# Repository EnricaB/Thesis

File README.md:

# Thesis
Thesis : Complessitá

---

### Clone this Repo

* navigate to your openFrameworks 0084 folder
  * `$ cd path/to/my_openFrameworks_0084/`
* inside this (root) folder, along side /apps /examples /addons etc, run: 
  * `$ git clone https://github.com/EnricaB/Thesis.git`
* now any OF apps inside of the openFrameworks folder of this repo will run fine

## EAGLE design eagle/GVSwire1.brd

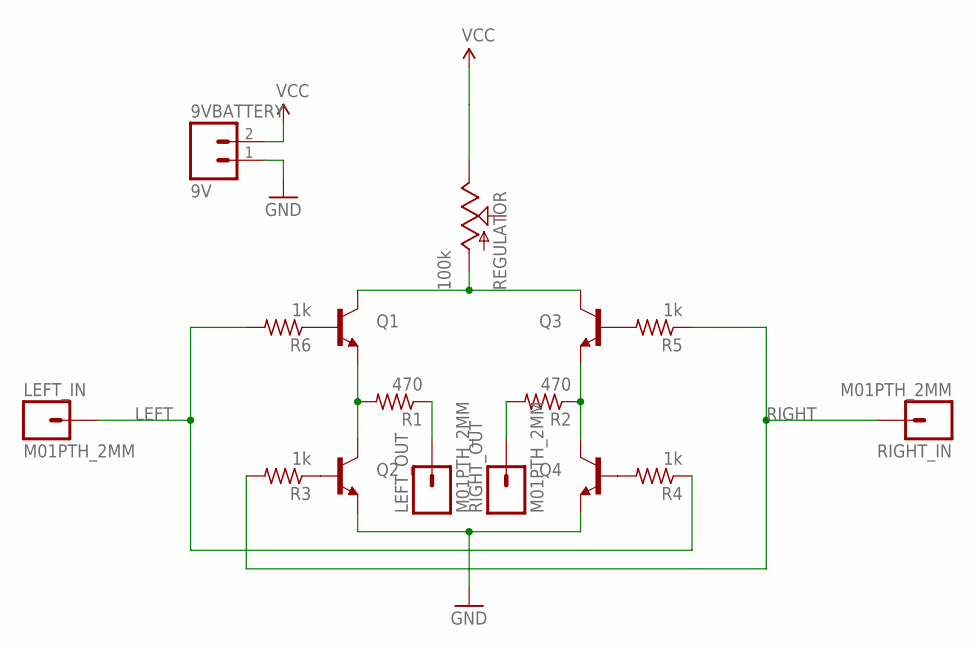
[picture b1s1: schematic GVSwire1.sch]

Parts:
9VBATTERY: 9V; 1X02_LONGPADS
LEFT_IN: M01PTH_2MM; 1X01_2MM
LEFT_OUT: M01PTH_2MM; 1X01_2MM
Q1, Q2, Q3, Q4: TRANSISTOR_NPNTO92; TO-92
R1, R2: 470; 0805-THM-7
R3, R4, R5, R6: 1k; 0805-THM-7
REGULATOR: 100k; ALPS_POT
RIGHT_IN: M01PTH_2MM; 1X01_2MM
RIGHT_OUT: M01PTH_2MM; 1X01_2MM

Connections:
GND: 9VBATTERY.1, Q2.1 (E), Q4.1 (E)
LEFT: LEFT_IN.1, R4.1, R6.2
unnamed: Q2.2 (B), R3.1
unnamed: Q4.2 (B), R4.2
unnamed: Q3.2 (B), R5.2
unnamed: Q1.2 (B), R6.1
unnamed: Q1.1 (E), Q2.3 (C), R1.2
unnamed: Q3.1 (E), Q4.3 (C), R2.1
unnamed: LEFT_OUT.1, R1.1
unnamed: R2.2, RIGHT_OUT.1
POT: Q1.3 (C), Q3.3 (C), REGULATOR.P$3 (A)
RIGHT: R3.2, R5.1, RIGHT_IN.1
VCC: 9VBATTERY.2, REGULATOR.P$1 (E)

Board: 2 copper layers, 16 parts (0 on the bottom side), 13 nets, no tracks yet.

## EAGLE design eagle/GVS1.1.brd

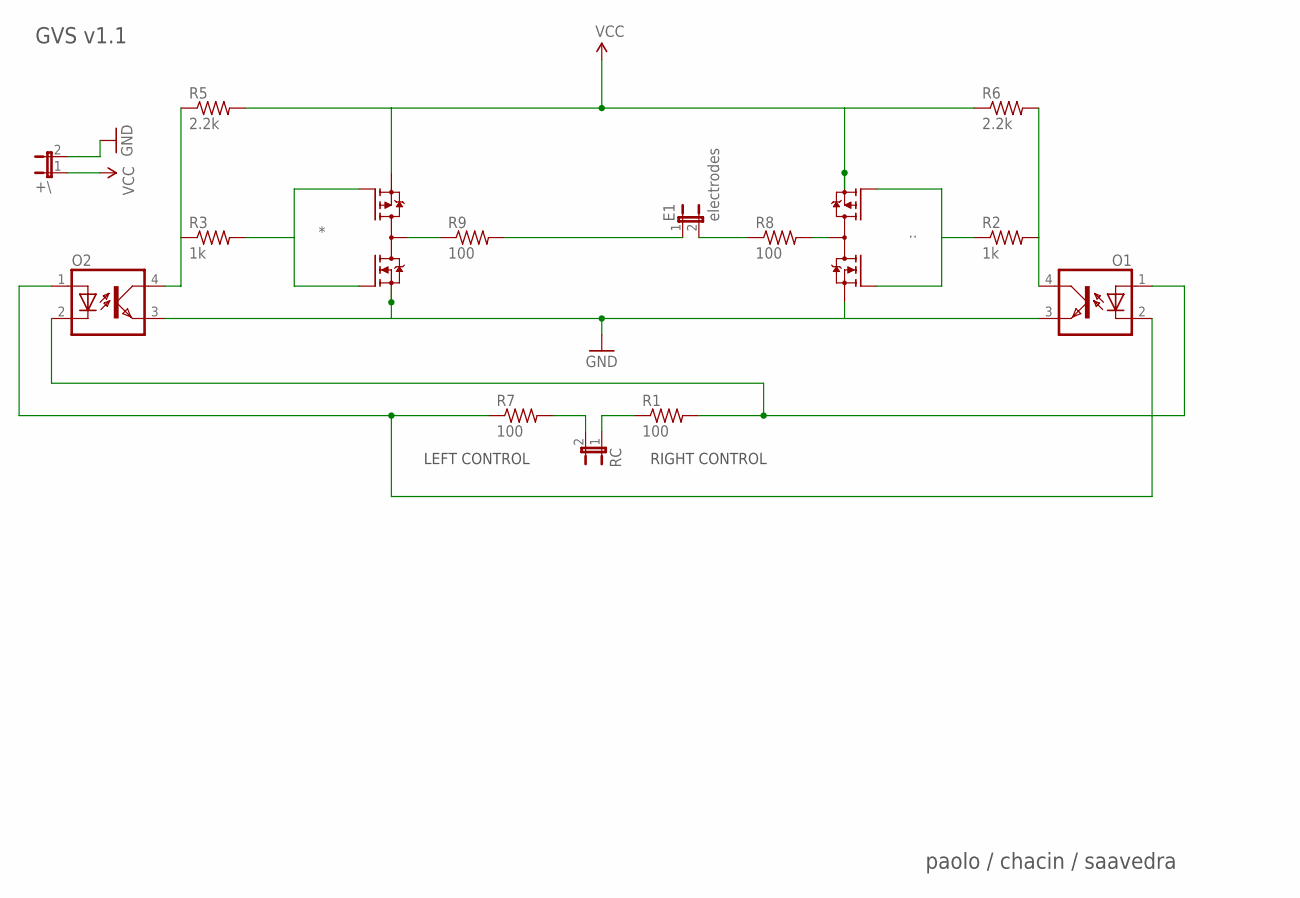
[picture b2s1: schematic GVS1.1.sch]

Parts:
*: IRF7389; SO08-IRF
+\: JP1E; JP1
..: IRF7389; SO08-IRF
E1: electrodes; JP1
O1, O2: SFH618A-2; DIP4
R1, R7, R8, R9: 100; 0805-THM-7
R2, R3: 1k; 0805-THM-7
R5, R6: 2.2k; 0805-THM-7
RC: JP1E; JP1

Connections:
+: *.3 (P-S), +\.1, ...3 (P-S), R5.2, R6.1
GND: *.1 (N-S), +\.2, ...1 (N-S), O1.3 (EMIT), O2.3 (EMIT)
unnamed: O2.4 (COL), R3.1, R5.1
unnamed: ...5 (D), ...6 (D), ...7 (D), ...8 (D), R8.2
unnamed: *.5 (D), *.6 (D), *.7 (D), *.8 (D), R9.1
unnamed: E1.1, R9.2
unnamed: E1.2, R8.1
unnamed: ...2 (N-G), ...4 (P-G), R2.1
unnamed: O1.4 (COL), R2.2, R6.2
unnamed: *.2 (N-G), *.4 (P-G), R3.2
unnamed: R7.2, RC.2
unnamed: R1.1, RC.1
unnamed: O1.2 (C), O2.1 (A), R7.1
unnamed: O1.1 (A), O2.2 (C), R1.2

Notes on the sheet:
RIGHT CONTROL
LEFT CONTROL
GVS v1.1
paolo / chacin / saavedra

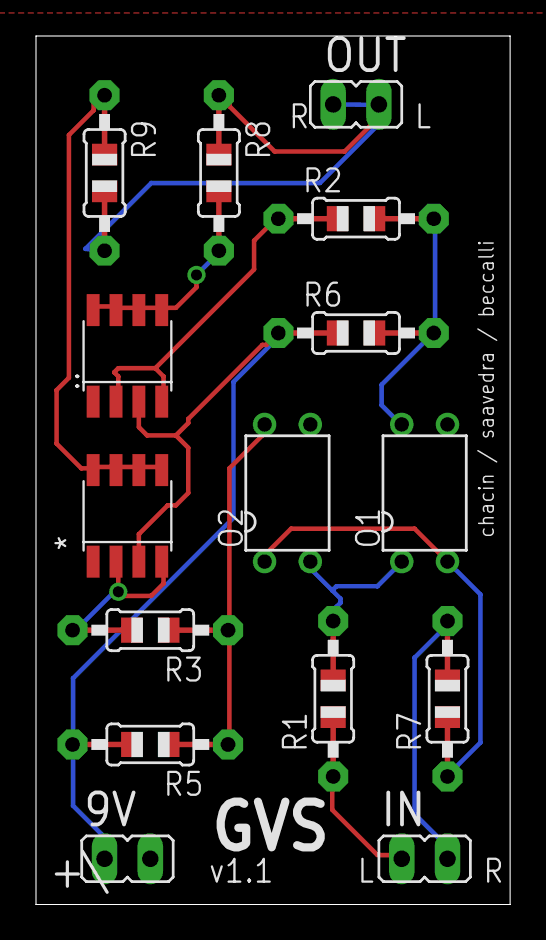
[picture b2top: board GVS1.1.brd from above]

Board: 2 copper layers, 26.3 x 48.2 mm, 15 parts (0 on the bottom side), 14 nets.

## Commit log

2015-04-08 added gitignore
2015-04-08 added arduino, eagle, and OF folders, example apps, eagle files
2015-04-09 updated original paolo circuit
2015-04-09 Thesis project: Complessitá
2015-05-06 code
2016-04-09 lots of updates!
2016-04-12 Create flock of birds video
2016-04-13 added arduino lib bkups
2016-04-13 added opening and closing titles with video and image assets
2016-04-14 added movies
2016-04-16 added t press check in update loop
2016-10-20 Create Complessita_DDD
2016-10-20 Create Updated oF
2016-10-20 Create update
    Updated to oF v0.9.4 for DDD
2016-10-20 Create bin
2016-10-20 Create data

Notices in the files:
parts and their libraries:
SparkFun: Licensing: CC v3.0 Share-Alike You are welcome to use this library for commercial purposes.
